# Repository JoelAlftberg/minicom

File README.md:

# MiniCOM

A small portable physical terminal computer running on the ATmega328p microprocessor.

- Custom keyboard QABKB
- Miniature custom RTOS called eeRTOS

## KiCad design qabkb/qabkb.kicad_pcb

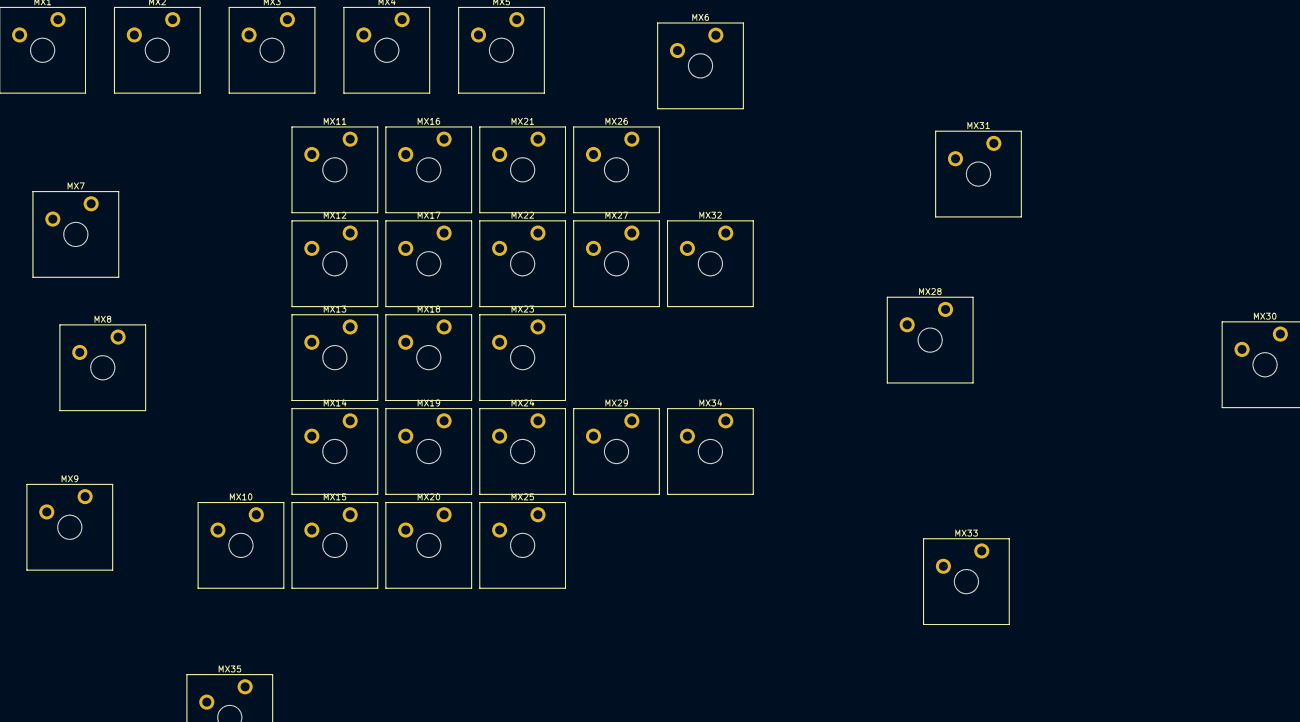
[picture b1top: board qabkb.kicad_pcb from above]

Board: 2 copper layers, 35 parts (0 on the bottom side), 10 nets, no tracks yet.

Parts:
MX1, MX2, MX3, MX4, MX5, MX6, MX7, MX8, MX9, MX11, MX12, MX13, MX14, MX15, MX16, MX17, MX18, MX19, MX22, MX23, MX24, MX25, MX26, MX27, MX28, MX29: MX_SW_solder; SW_Cherry_MX_Plate_1.00u
MX10, MX34: MX_SW_solder; SW_Cherry_MX_Plate_1.75u
MX20: MX_SW_solder; SW_Cherry_MX_Plate_1.50u
MX21, MX31, MX32, MX35: MX_SW_solder; SW_Cherry_MX_Plate_1.25u
MX30: MX_SW_solder; SW_Cherry_MX_Plate_ISOEnter
MX33: MX_SW_solder; SW_Cherry_MX_Plate_2.75u

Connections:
/Col1: MX1.1, MX11.1, MX21.1, MX31.1
/Col2: MX2.1, MX12.1, MX22.1, MX32.1
/Col3: MX3.1, MX13.1, MX23.1, MX33.1
/Col4: MX4.1, MX14.1, MX24.1, MX34.1
/Col5: MX5.1, MX15.1, MX25.1, MX35.1
/Col6: MX6.1, MX16.1, MX26.1
/Col7: MX7.1, MX17.1, MX27.1
/Col8: MX8.1, MX18.1, MX28.1
/Col9: MX9.1, MX19.1, MX29.1
/Col10: MX10.1, MX20.1, MX30.1

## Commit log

2025-10-17 Adds TCB init and create
2025-10-19 Restructure repo
2025-10-20 Adds priority queue
